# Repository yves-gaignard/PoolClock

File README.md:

# PoolClock
Swimming pool clock with code base for a completely customizable and configurable LED clock using WS2812b RGB LEDs. Controllable via the Blynk app

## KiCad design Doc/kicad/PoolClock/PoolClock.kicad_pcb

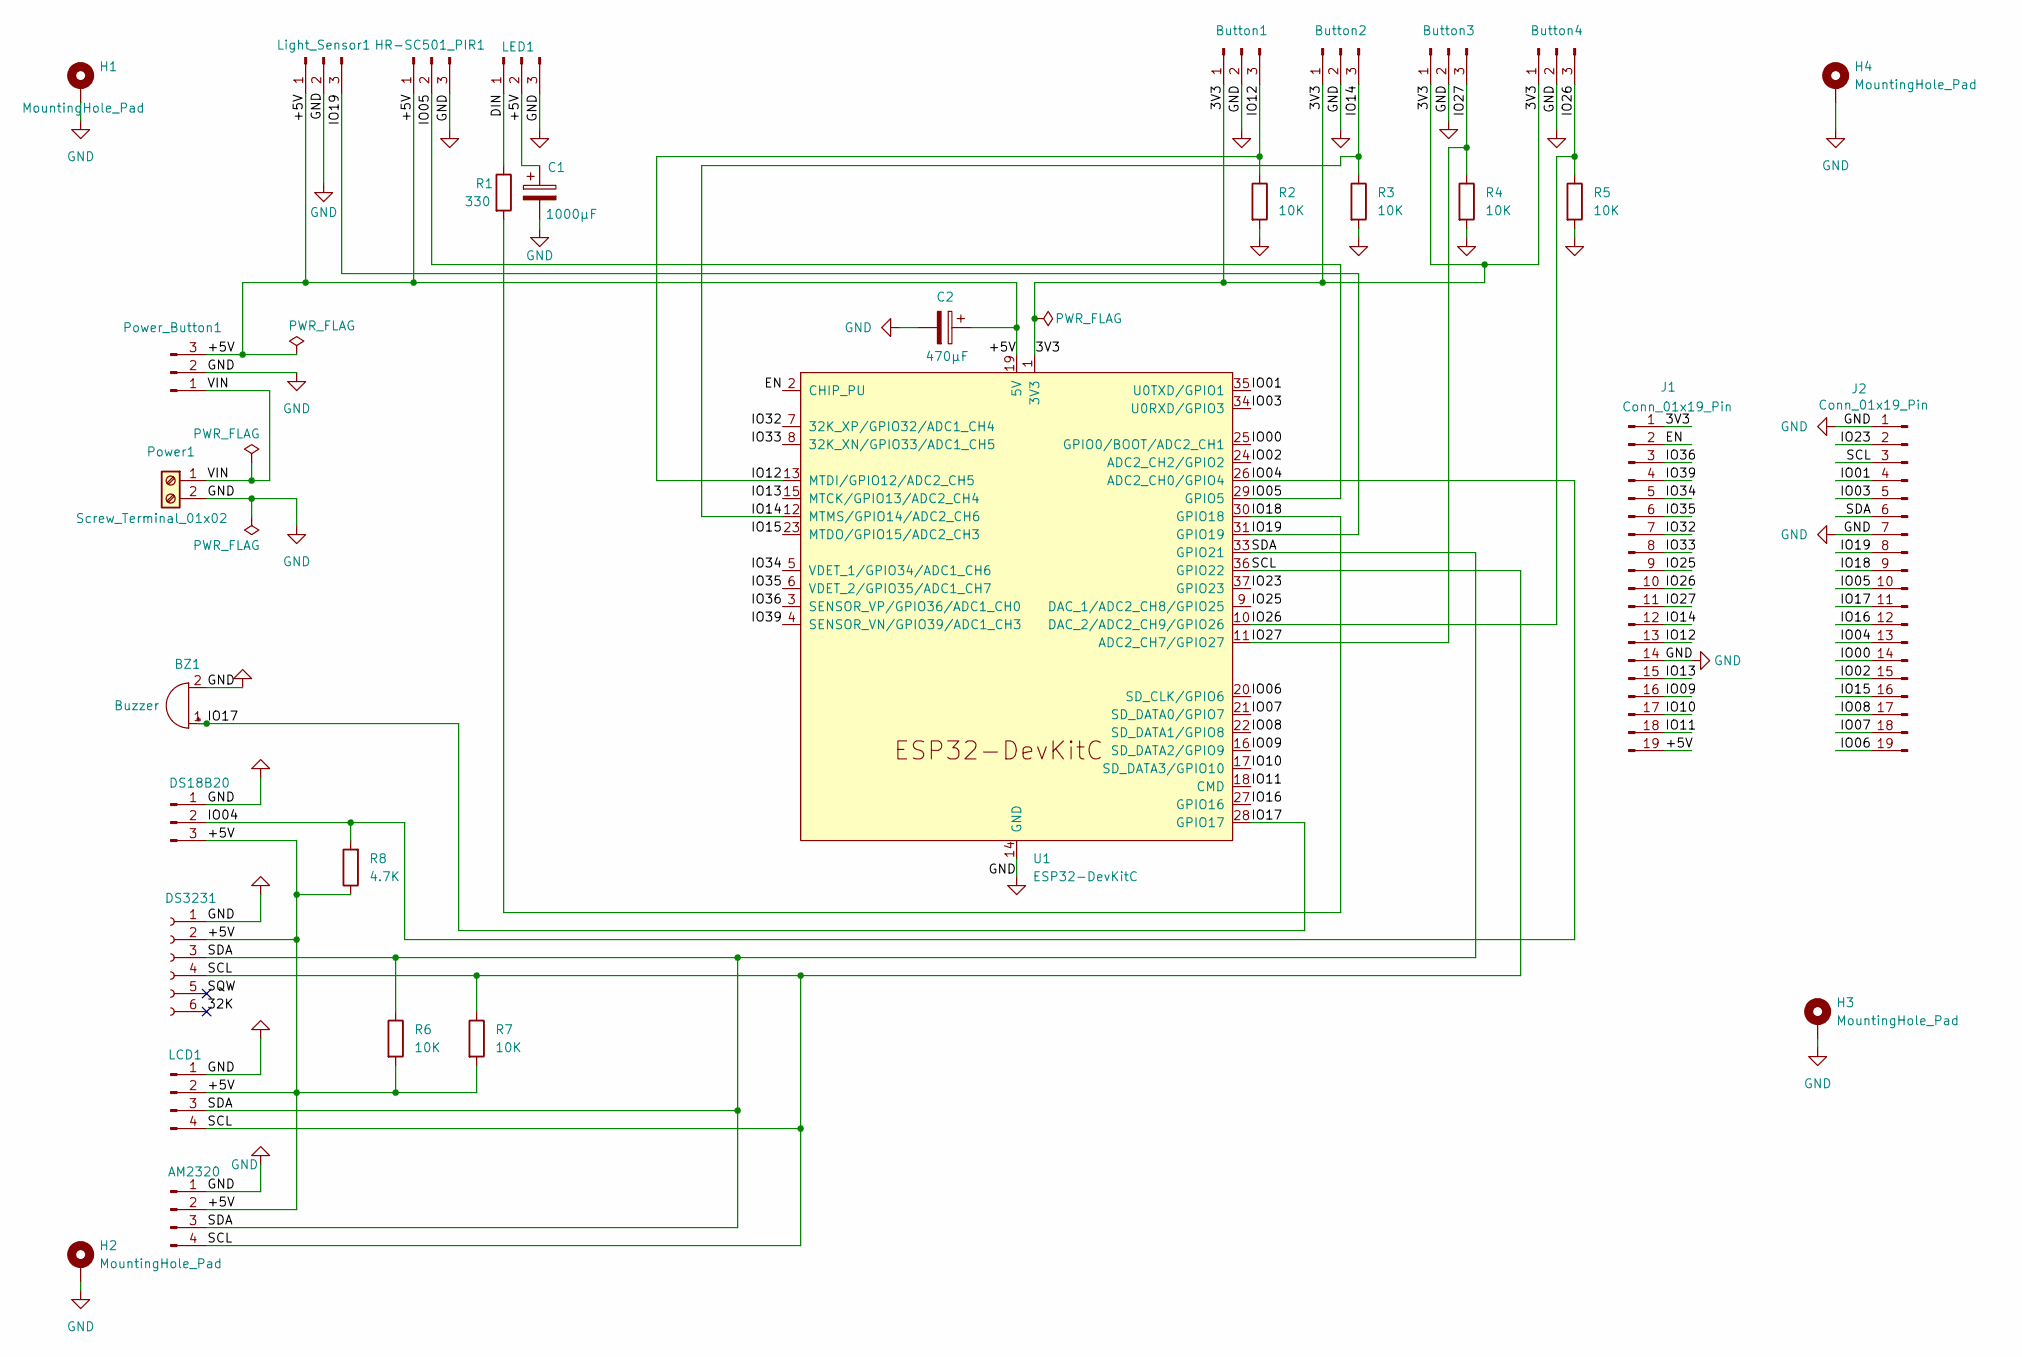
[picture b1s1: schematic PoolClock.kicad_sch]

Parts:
AM2320: Conn_01x04_Pin; JST_EH_B4B-EH-A_1x04_P2.50mm_Vertical
BZ1: Buzzer; JST_EH_B2B-EH-A_1x02_P2.50mm_Vertical
Button1, Button2, Button3, Button4: Conn_01x03_Pin; JST_EH_B3B-EH-A_1x03_P2.50mm_Vertical
C1: 1000µF; C_Radial_D10.0mm_H16.0mm_P5.00mm
C2: 470µF; C_Radial_D8.0mm_H11.5mm_P3.50mm
DS18B20: Conn_01x03_Pin; JST_EH_B3B-EH-A_1x03_P2.50mm_Vertical
DS3231: Conn_01x06_Socket; PinSocket_1x06_P2.54mm_Horizontal
H1, H2, H3, H4: MountingHole_Pad; MountingHole_3.2mm_M3_DIN965_Pad
HR-SC501_PIR1: Conn_01x03_Pin; JST_EH_B3B-EH-A_1x03_P2.50mm_Vertical
J1, J2: Conn_01x19_Pin; PinSocket_1x19_P2.54mm_Vertical
LCD1: Conn_01x04_Pin; JST_EH_B4B-EH-A_1x04_P2.50mm_Vertical
LED1: Conn_01x03_Pin; JST_EH_B3B-EH-A_1x03_P2.50mm_Vertical
Light_Sensor1: Conn_01x03_Pin; JST_EH_B3B-EH-A_1x03_P2.50mm_Vertical
Power1: Screw_Terminal_01x02; HANDSON_KF301-2P
Power_Button1: Conn_01x03_Pin; JST_EH_B3B-EH-A_1x03_P2.50mm_Vertical
R1: 330; R_Axial_DIN0207_L6.3mm_D2.5mm_P7.62mm_Horizontal
R2, R3, R4, R5, R6, R7: 10K; R_Axial_DIN0207_L6.3mm_D2.5mm_P7.62mm_Horizontal
R8: 4.7K; R_Axial_DIN0207_L6.3mm_D2.5mm_P7.62mm_Horizontal
U1: ESP32-DevKitC

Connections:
/3V3: Button1.1, Button2.1, Button3.1, Button4.1, J1.1, U1.1 (3V3)
/32K: DS3231.6
/+5V: AM2320.2, C1.1, C2.1, DS18B20.3, DS3231.2, HR-SC501_PIR1.1, J1.19, LCD1.2, LED1.2, Light_Sensor1.1, Power_Button1.3, R6.2, R7.2, R8.1, U1.19 (5V)
/DIN: LED1.1, R1.1
/EN: J1.2, U1.2 (CHIP_PU)
/IO00: J2.14, U1.25 (GPIO0/BOOT/ADC2_CH1)
/IO01: J2.4, U1.35 (U0TXD/GPIO1)
/IO02: J2.15, U1.24 (ADC2_CH2/GPIO2)
/IO03: J2.5, U1.34 (U0RXD/GPIO3)
/IO04: DS18B20.2, J2.13, R8.2, U1.26 (ADC2_CH0/GPIO4)
/IO05: HR-SC501_PIR1.2, J2.10, U1.29 (GPIO5)
/IO06: J2.19, U1.20 (SD_CLK/GPIO6)
/IO07: J2.18, U1.21 (SD_DATA0/GPIO7)
/IO08: J2.17, U1.22 (SD_DATA1/GPIO8)
/IO09: J1.16, U1.16 (SD_DATA2/GPIO9)
/IO10: J1.17, U1.17 (SD_DATA3/GPIO10)
/IO11: J1.18, U1.18 (CMD)
/IO12: Button1.3, J1.13, R2.1, U1.13 (MTDI/GPIO12/ADC2_CH5)
/IO13: J1.15, U1.15 (MTCK/GPIO13/ADC2_CH4)
/IO14: Button2.3, J1.12, R3.1, U1.12 (MTMS/GPIO14/ADC2_CH6)
/IO15: J2.16, U1.23 (MTDO/GPIO15/ADC2_CH3)
/IO16: J2.12, U1.27 (GPIO16)
/IO17: BZ1.1 (+), J2.11, U1.28 (GPIO17)
/IO18: J2.9, R1.2, U1.30 (GPIO18)
/IO19: J2.8, Light_Sensor1.3, U1.31 (GPIO19)
/IO23: J2.2, U1.37 (GPIO23)
/IO25: J1.9, U1.9 (DAC_1/ADC2_CH8/GPIO25)
/IO26: Button4.3, J1.10, R5.1, U1.10 (DAC_2/ADC2_CH9/GPIO26)
/IO27: Button3.3, J1.11, R4.1, U1.11 (ADC2_CH7/GPIO27)
/IO32: J1.7, U1.7 (32K_XP/GPIO32/ADC1_CH4)
/IO33: J1.8, U1.8 (32K_XN/GPIO33/ADC1_CH5)
/IO34: J1.5, U1.5 (VDET_1/GPIO34/ADC1_CH6)
/IO35: J1.6, U1.6 (VDET_2/GPIO35/ADC1_CH7)
/IO36: J1.3, U1.3 (SENSOR_VP/GPIO36/ADC1_CH0)
/IO39: J1.4, U1.4 (SENSOR_VN/GPIO39/ADC1_CH3)
/SCL: AM2320.4, DS3231.4, J2.3, LCD1.4, R7.1, U1.36 (GPIO22)
/SDA: AM2320.3, DS3231.3, J2.6, LCD1.3, R6.1, U1.33 (GPIO21)
/SQW: DS3231.5
/VIN: Power1.1, Power_Button1.1
GND: AM2320.1, BZ1.2 (-), Button1.2, Button2.2, Button3.2, Button4.2, C1.2, C2.2, DS18B20.1, DS3231.1, H1.1, H2.1, H3.1, H4.1, HR-SC501_PIR1.3, J1.14, J2.1, J2.7, LCD1.1, LED1.3, Light_Sensor1.2, Power1.2, Power_Button1.2, R2.2, R3.2, R4.2, R5.2, U1.14 (GND), U1.32 (GND), U1.38 (GND)

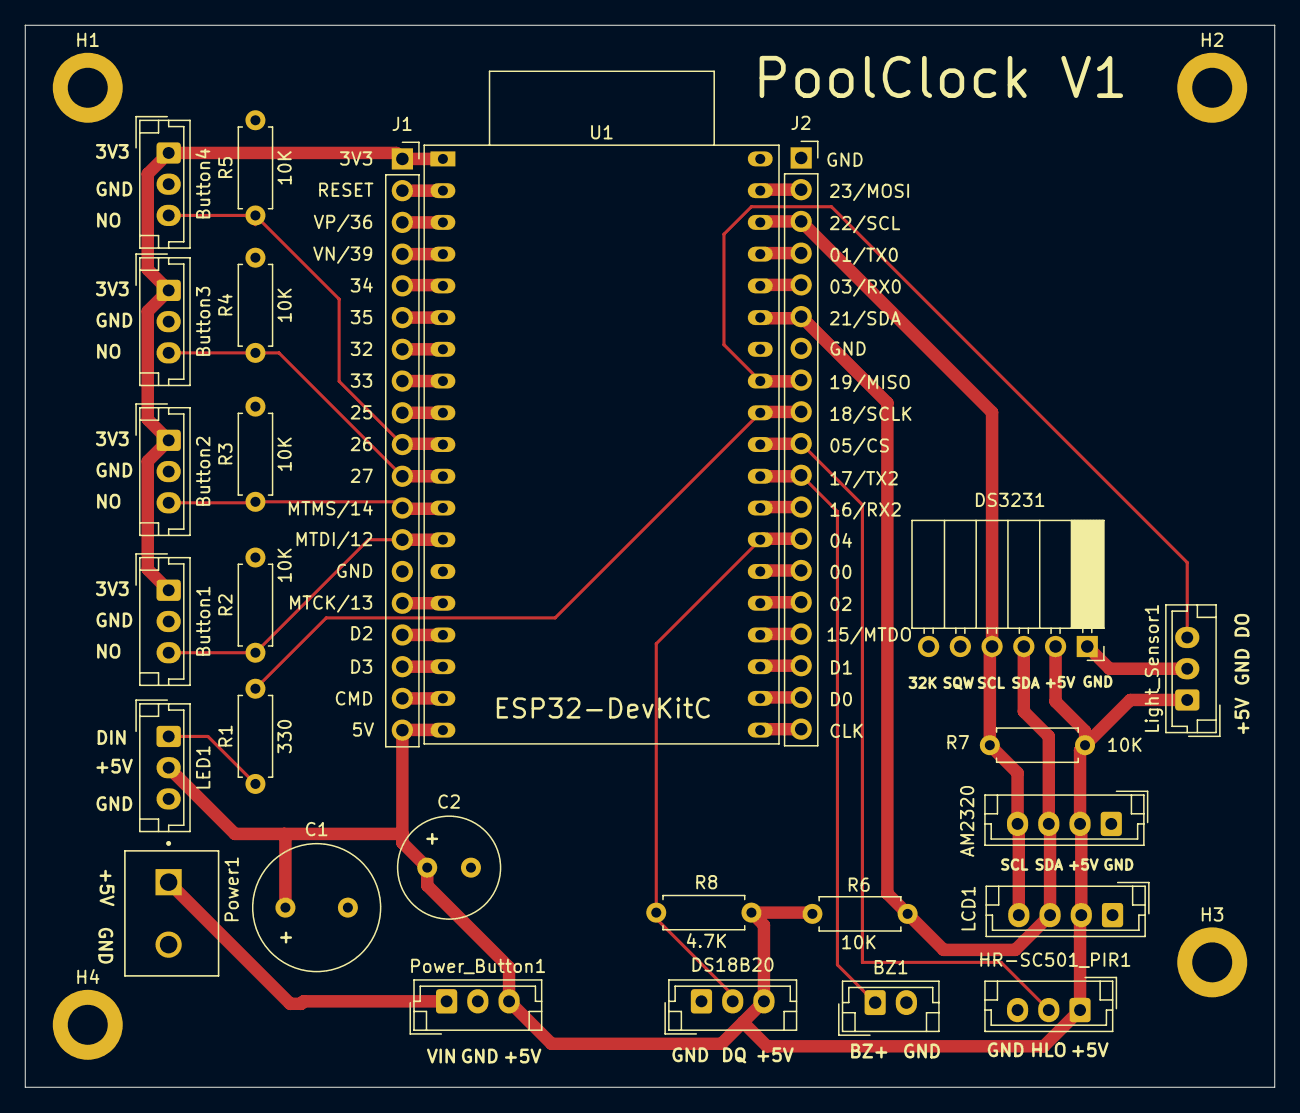
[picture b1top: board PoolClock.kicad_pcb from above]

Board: 2 copper layers, 100.0 x 85.0 mm, 31 parts (0 on the bottom side), 38 nets.

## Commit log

2023-05-07 first delivery
2023-05-09 remove HALF_SEGMENT
2023-05-09 ren ShelfDsiplays to PoolClockDisplays
2023-05-21 add wiring diagram
2023-06-09 first working test
2023-06-11 adding temperature display
2023-06-13 fritzing
2023-06-16 add Log and temperture management
2023-07-20 externalization of secrets
2023-07-29 add AM232X sensor
2023-07-29 PIR motion integration
2023-07-31 LCD integration
2023-08-03 creating doc directory
2023-08-07 3DFIles delivery
2023-08-07 Delivery of 3DFIles
2023-08-08 change electronic schema
2023-08-08 replace ArduineOTA by AsyncElegantOTA
2023-08-08 add webserver page
2023-08-08 add favicon
2023-08-09 modify webserial page
2023-08-09 deployment of LogManager
2023-08-10 add LogManager everywhere
2023-08-14 add Buzzer Manager
2023-08-14 add TAG in main.cpp
2023-08-16 add one transition in the FSM
2024-01-04 evolutions
2025-01-08 state machine management
2025-01-09 before poolCmd removal
2025-01-10 fix EasyButton and AM232X read
2025-01-12 PIR motion is working
2025-01-13 add buzzer and LDR management
2025-01-15 add OTAUpdate modification
2025-01-29 delivery of PoolCLock Kicad files
